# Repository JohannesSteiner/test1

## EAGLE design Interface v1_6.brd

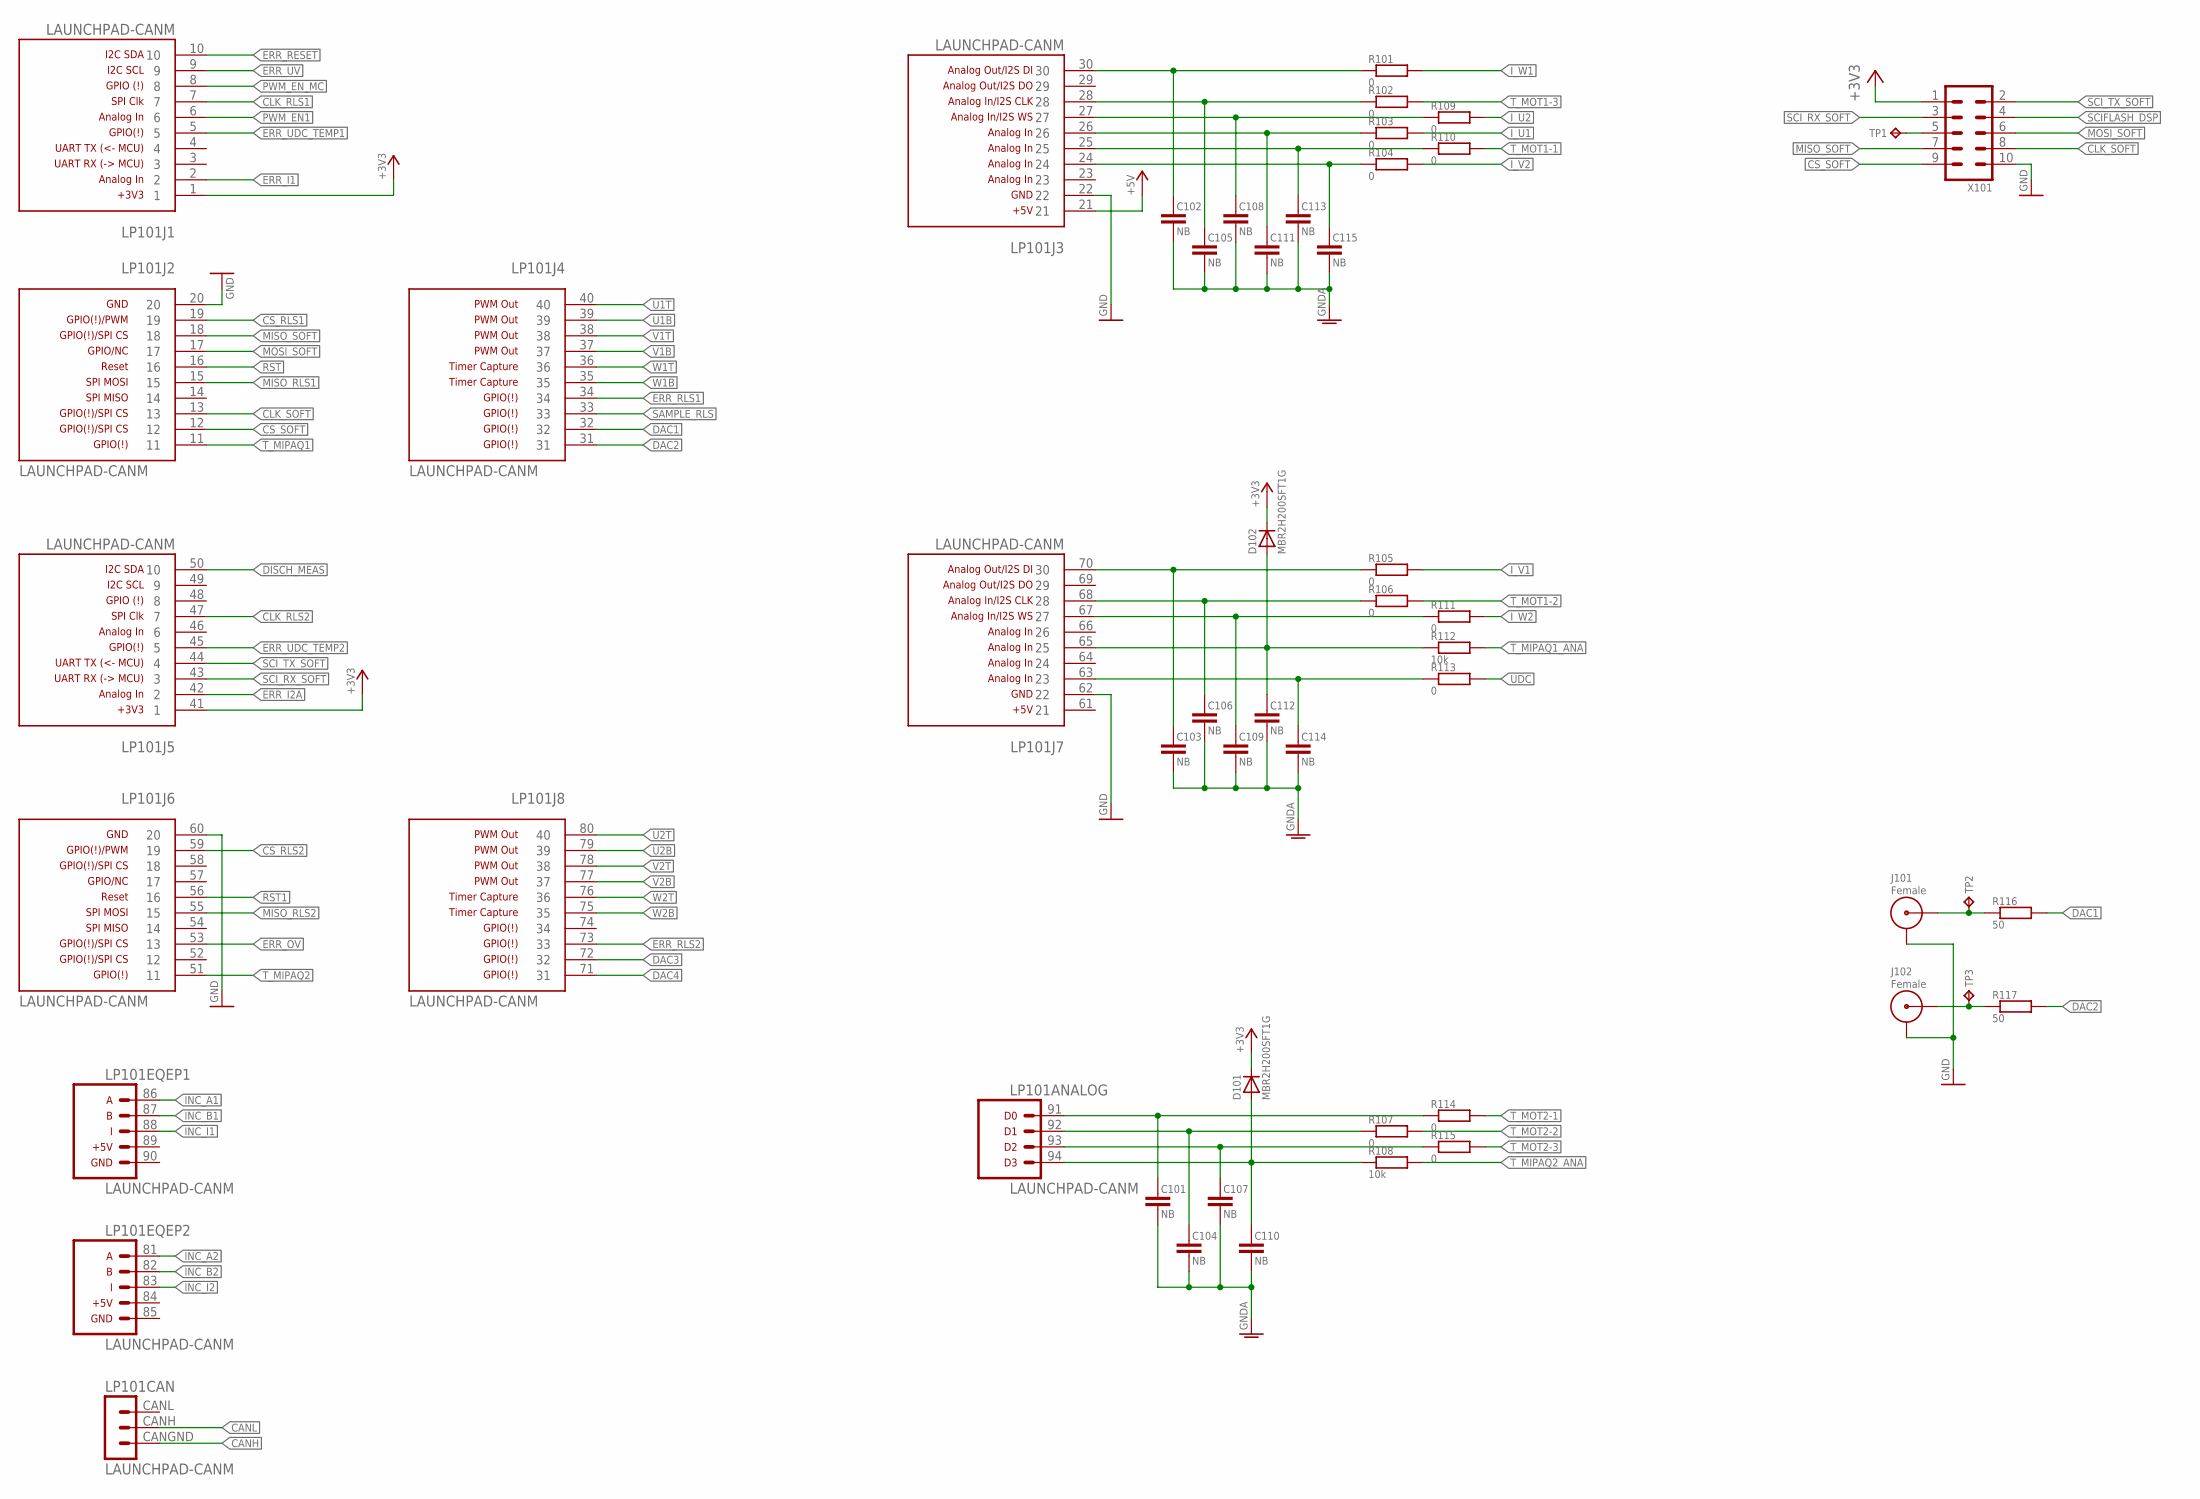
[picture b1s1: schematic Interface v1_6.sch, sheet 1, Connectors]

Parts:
C101, C102, C103, C104, C105, C106, C107, C108, C109, C110, C111, C112, C113, C114, C115: NB; C-0805"
D101, D102: MBR2H200SFT1G; D-0805"
J101, J102: Female; SMA_KLEIN
LP101: LAUNCHPAD-CANM; LAUNCHPAD_M
R101, R102, R103, R104, R105, R106, R107, R109, R110, R111, R113, R114, R115: 0; R-0805"
R108, R112: 10k; R-0805"
R116, R117: 50; R-0805"
TP1: TP-TH-08; TP-08
TP2, TP3: TP-TH-12; TP-12
X101: Softauge; ML-2~10

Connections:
+3V3: D101.C, D102.C, LP101.1, LP101.41 (1), X101.1; also elsewhere on the board
+5V: LP101.21; also elsewhere on the board
ADCIN15: C114.1, LP101.63 (23), R113.1
ADCINA0: C102.1, LP101.30, R101.1
ADCINA1: C103.1, LP101.70 (30), R105.1
ADCINA3: C111.1, LP101.26, R103.1
ADCINB2: C105.1, LP101.28, R102.1
ADCINB3: C113.1, LP101.25, R110.1
ADCINB4: C106.1, LP101.68 (28), R106.1
ADCINB5: C112.1, D102.A, LP101.65 (25), R112.1
ADCINC2: C108.1, LP101.27, R109.1
ADCINC3: C115.1, LP101.24, R104.1
ADCIND0: C101.1, LP101.91 (D0), R114.1
ADCIND1: C104.1, LP101.92 (D1), R107.1
ADCIND2: C107.1, LP101.93 (D2), R115.1
ADCIND3: C110.1, D101.A, LP101.94 (D3), R108.1
CANH: LP101.CANGND (1); also elsewhere on the board
CANL: LP101.CANH (2); also elsewhere on the board
CLK_RLS1: LP101.7; also elsewhere on the board
CLK_RLS2: LP101.47 (7); also elsewhere on the board
CLK_SOFT: LP101.13, X101.8
CS_RLS1: LP101.19; also elsewhere on the board
CS_RLS2: LP101.59 (19); also elsewhere on the board
CS_SOFT: LP101.12, X101.9
DAC1: LP101.32, R116.2
DAC2: LP101.31, R117.2
DAC3: LP101.72 (32)
DAC4: LP101.71 (31)
DISCH_MEAS: LP101.50 (10); also elsewhere on the board
ERR_I1: LP101.2; also elsewhere on the board
ERR_I2A: LP101.42 (2); also elsewhere on the board
ERR_OV: LP101.53 (13); also elsewhere on the board
ERR_RESET: LP101.10; also elsewhere on the board
ERR_RLS1: LP101.34
ERR_RLS2: LP101.73 (33)
ERR_UDC_TEMP1: LP101.5; also elsewhere on the board
ERR_UDC_TEMP2: LP101.45 (5); also elsewhere on the board
ERR_UV: LP101.9; also elsewhere on the board
GND: J101.1 (GND), J101.3 (GND), J101.4 (GND), J101.5 (GND), J102.1 (GND), J102.3 (GND), J102.4 (GND), J102.5 (GND), LP101.20, LP101.22, LP101.60 (20), LP101.62 (22), X101.10; also elsewhere on the board
GNDA: C101.2, C102.2, C103.2, C104.2, C105.2, C106.2, C107.2, C108.2, C109.2, C110.2, C111.2, C112.2, C113.2, C114.2, C115.2; also elsewhere on the board
INC_A1: LP101.86 (1); also elsewhere on the board
INC_A2: LP101.81 (1); also elsewhere on the board
INC_B1: LP101.87 (2); also elsewhere on the board
INC_B2: LP101.82 (2); also elsewhere on the board
INC_I1: LP101.88 (3); also elsewhere on the board
INC_I2: LP101.83 (3); also elsewhere on the board
I_U1: R103.2; also elsewhere on the board
I_U2: R109.2; also elsewhere on the board
I_V1: R105.2; also elsewhere on the board
I_V2: R104.2; also elsewhere on the board
I_W1: R101.2; also elsewhere on the board
I_W2: R111.2; also elsewhere on the board
MISO_RLS1: LP101.15; also elsewhere on the board
MISO_RLS2: LP101.55 (15); also elsewhere on the board
MISO_SOFT: LP101.18, X101.7
MOSI_SOFT: LP101.17, X101.6
unnamed: C109.1, LP101.67 (27), R111.1
unnamed: TP1.TP, X101.5
unnamed: J102.SIG, R117.1, TP3.TP
unnamed: J101.SIG, R116.1, TP2.TP
PWM_EN1: LP101.6; also elsewhere on the board
PWM_EN_MC: LP101.8; also elsewhere on the board
RST: LP101.16
RST1: LP101.56 (16)
SAMPLE_RLS: LP101.33; also elsewhere on the board
SCIFLASH_DSP: X101.4
SCI_RX_SOFT: LP101.43 (3), X101.3
SCI_TX_SOFT: LP101.44 (4), X101.2
T_MIPAQ1: LP101.11; also elsewhere on the board
T_MIPAQ1_ANA: R112.2; also elsewhere on the board
T_MIPAQ2: LP101.51 (11); also elsewhere on the board
T_MIPAQ2_ANA: R108.2; also elsewhere on the board
T_MOT1-1: R110.2; also elsewhere on the board
T_MOT1-2: R106.2; also elsewhere on the board
T_MOT1-3: R102.2; also elsewhere on the board
T_MOT2-1: R114.2; also elsewhere on the board
T_MOT2-2: R107.2; also elsewhere on the board
T_MOT2-3: R115.2; also elsewhere on the board
U1B: LP101.39; also elsewhere on the board
U1T: LP101.40; also elsewhere on the board
U2B: LP101.79 (39); also elsewhere on the board
U2T: LP101.80 (40); also elsewhere on the board
UDC: R113.2; also elsewhere on the board
V1B: LP101.37; also elsewhere on the board
V1T: LP101.38; also elsewhere on the board
V2B: LP101.77 (37); also elsewhere on the board
V2T: LP101.78 (38); also elsewhere on the board
W1B: LP101.35; also elsewhere on the board
W1T: LP101.36; also elsewhere on the board
W2B: LP101.75 (35); also elsewhere on the board
W2T: LP101.76 (36); also elsewhere on the board

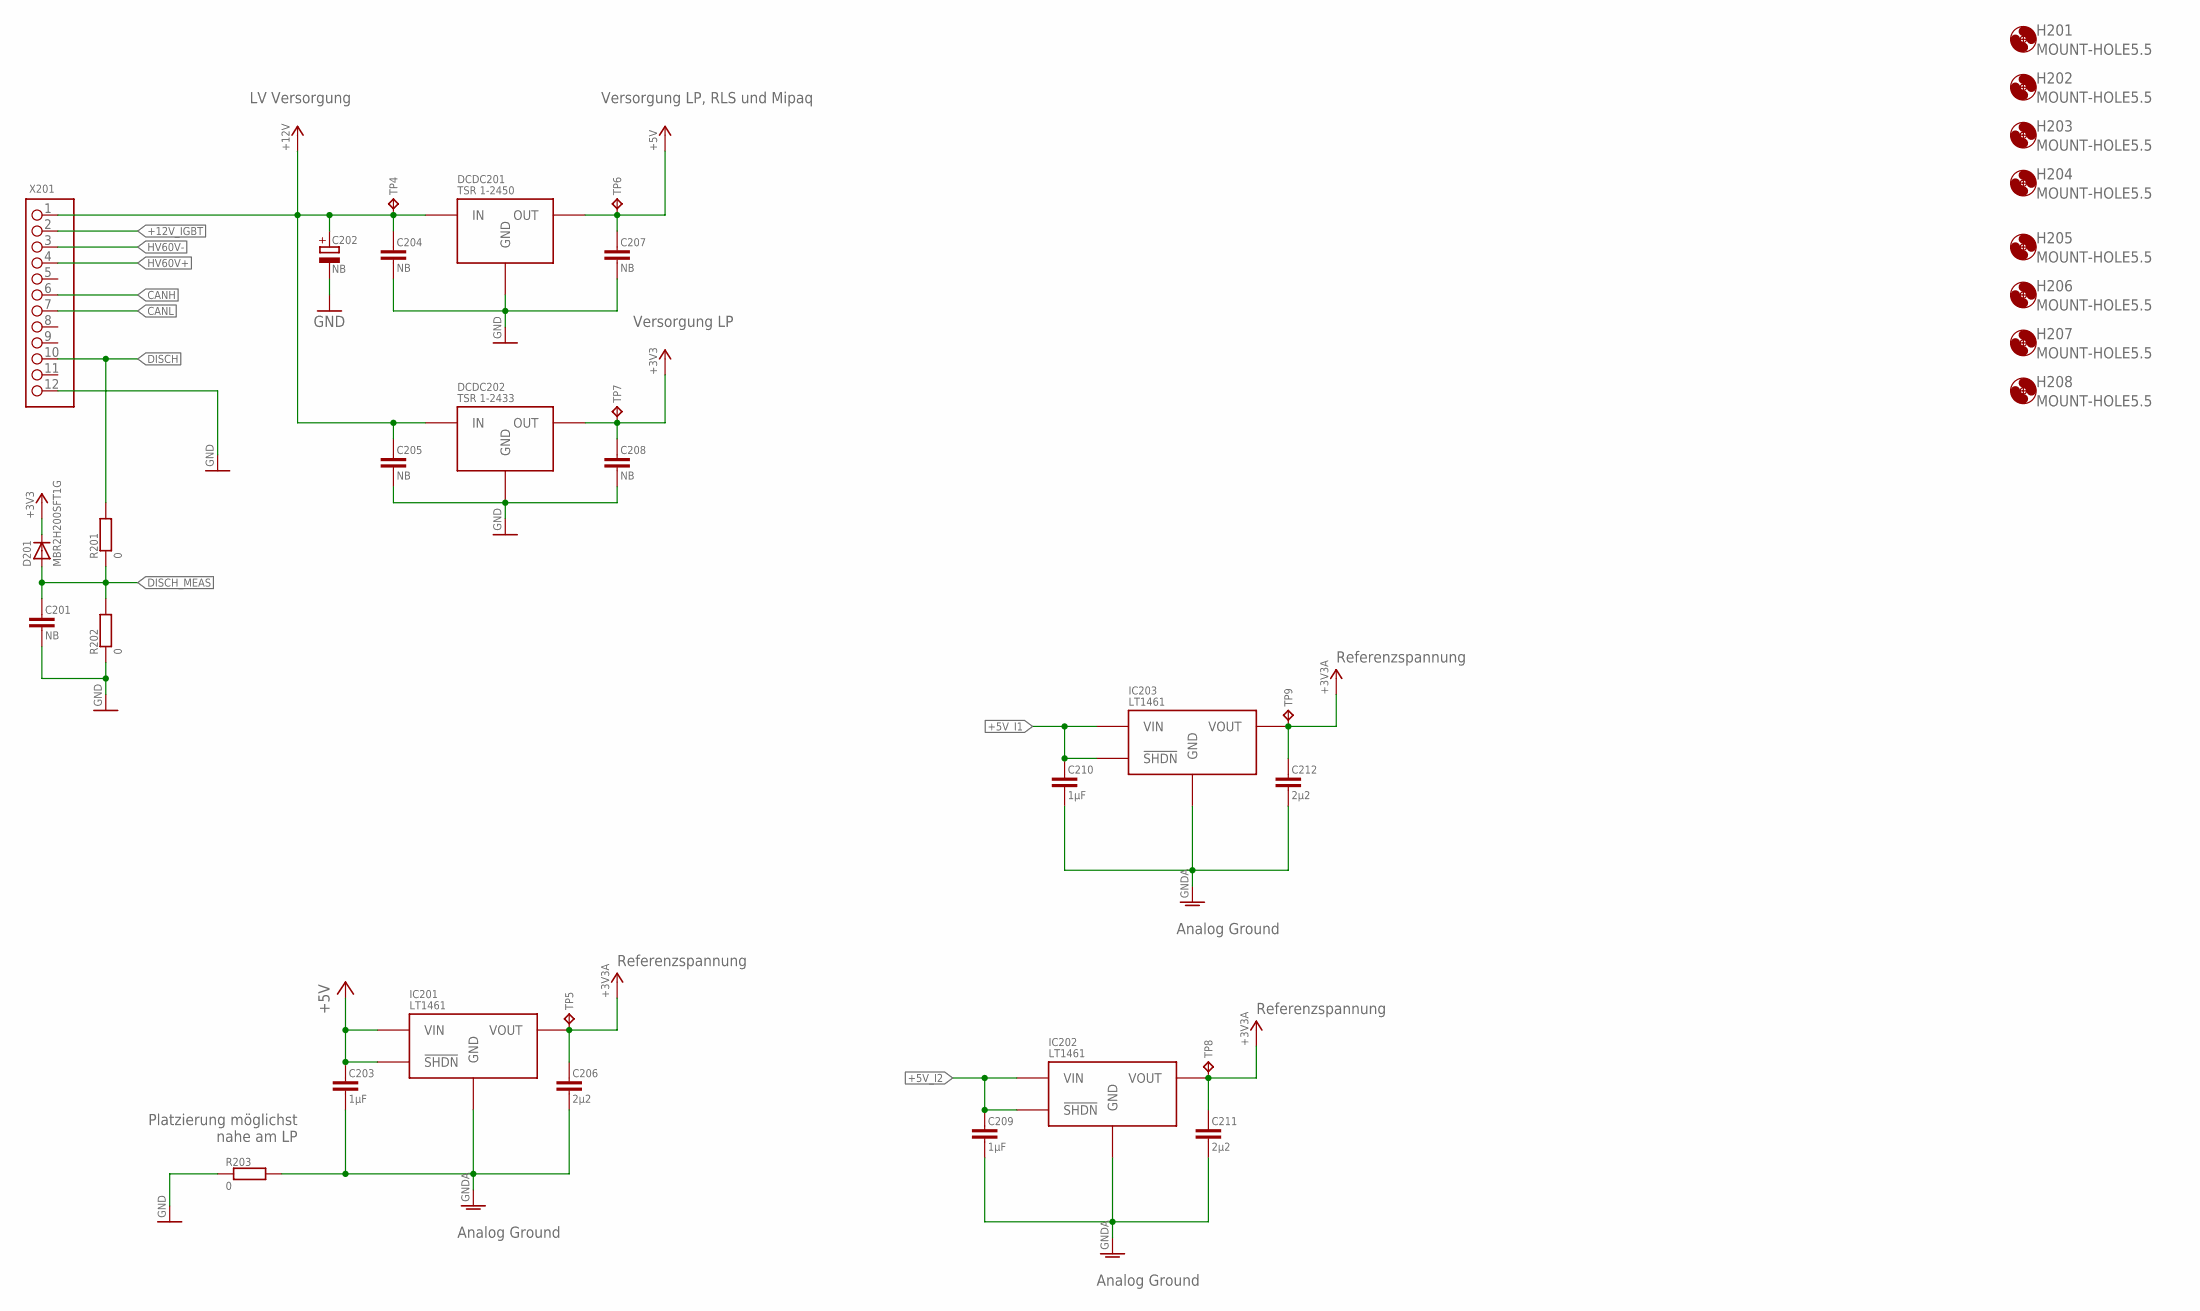
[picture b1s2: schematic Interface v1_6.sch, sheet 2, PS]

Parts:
C201, C204, C205, C207, C208: NB; C-0805"
C202: NB; CP-1210"
C203, C209, C210: 1µF; C-0805"
C206, C211, C212: 2µ2; C-0805"
D201: MBR2H200SFT1G; D-0805"
DCDC201: TSR 1-2450; TSR-1
DCDC202: TSR 1-2433; TSR-1
H201, H202, H203, H204, H205, H206, H207, H208: MOUNT-HOLE5.5; 5,5
IC201, IC202, IC203: LT1461; SO8
R201, R202, R203: 0; R-0805"
TP4, TP5, TP6, TP7, TP8, TP9: TP-TH-12; TP-12
X201: MINIBRIDGE12-GERADE

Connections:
+3V3: C208.1, D201.C, DCDC202.3 (OUT), TP7.TP; also elsewhere on the board
+3V3A: C206.1, IC201.6 (VOUT), TP5.TP; also elsewhere on the board
+3V3A_I1: C212.1, IC203.6 (VOUT), TP9.TP; also elsewhere on the board
+3V3A_I2: C211.1, IC202.6 (VOUT), TP8.TP; also elsewhere on the board
+5V: C203.1, C207.1, DCDC201.3 (OUT), IC201.2 (VIN), IC201.3 (!SHDN), TP6.TP; also elsewhere on the board
+5V_I1: C210.1, IC203.2 (VIN), IC203.3 (!SHDN); also elsewhere on the board
+5V_I2: C209.1, IC202.2 (VIN), IC202.3 (!SHDN); also elsewhere on the board
+12V: C202.+, C204.1, C205.1, DCDC201.1 (IN), DCDC202.1 (IN), TP4.TP, X201.1; also elsewhere on the board
+12V_IGBT: X201.2; also elsewhere on the board
CANH: X201.6; also elsewhere on the board
CANL: X201.7; also elsewhere on the board
DISCH: R201.2, X201.10; also elsewhere on the board
DISCH_MEAS: C201.1, D201.A, R201.1, R202.2; also elsewhere on the board
GND: C201.2, C202.-, C204.2, C205.2, C207.2, C208.2, DCDC201.2 (GND), DCDC202.2 (GND), R202.1, R203.1, X201.12; also elsewhere on the board
GNDA: C203.2, C206.2, C209.2, C210.2, C211.2, C212.2, IC201.4 (GND), IC202.4 (GND), IC203.4 (GND), R203.2; also elsewhere on the board
HV60V+: X201.4; also elsewhere on the board
HV60V-: X201.3; also elsewhere on the board

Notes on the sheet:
LV Versorgung
Versorgung LP, RLS und Mipaq
Versorgung LP
Referenzspannung
Analog Ground
Platzierung möglichst nahe am LP

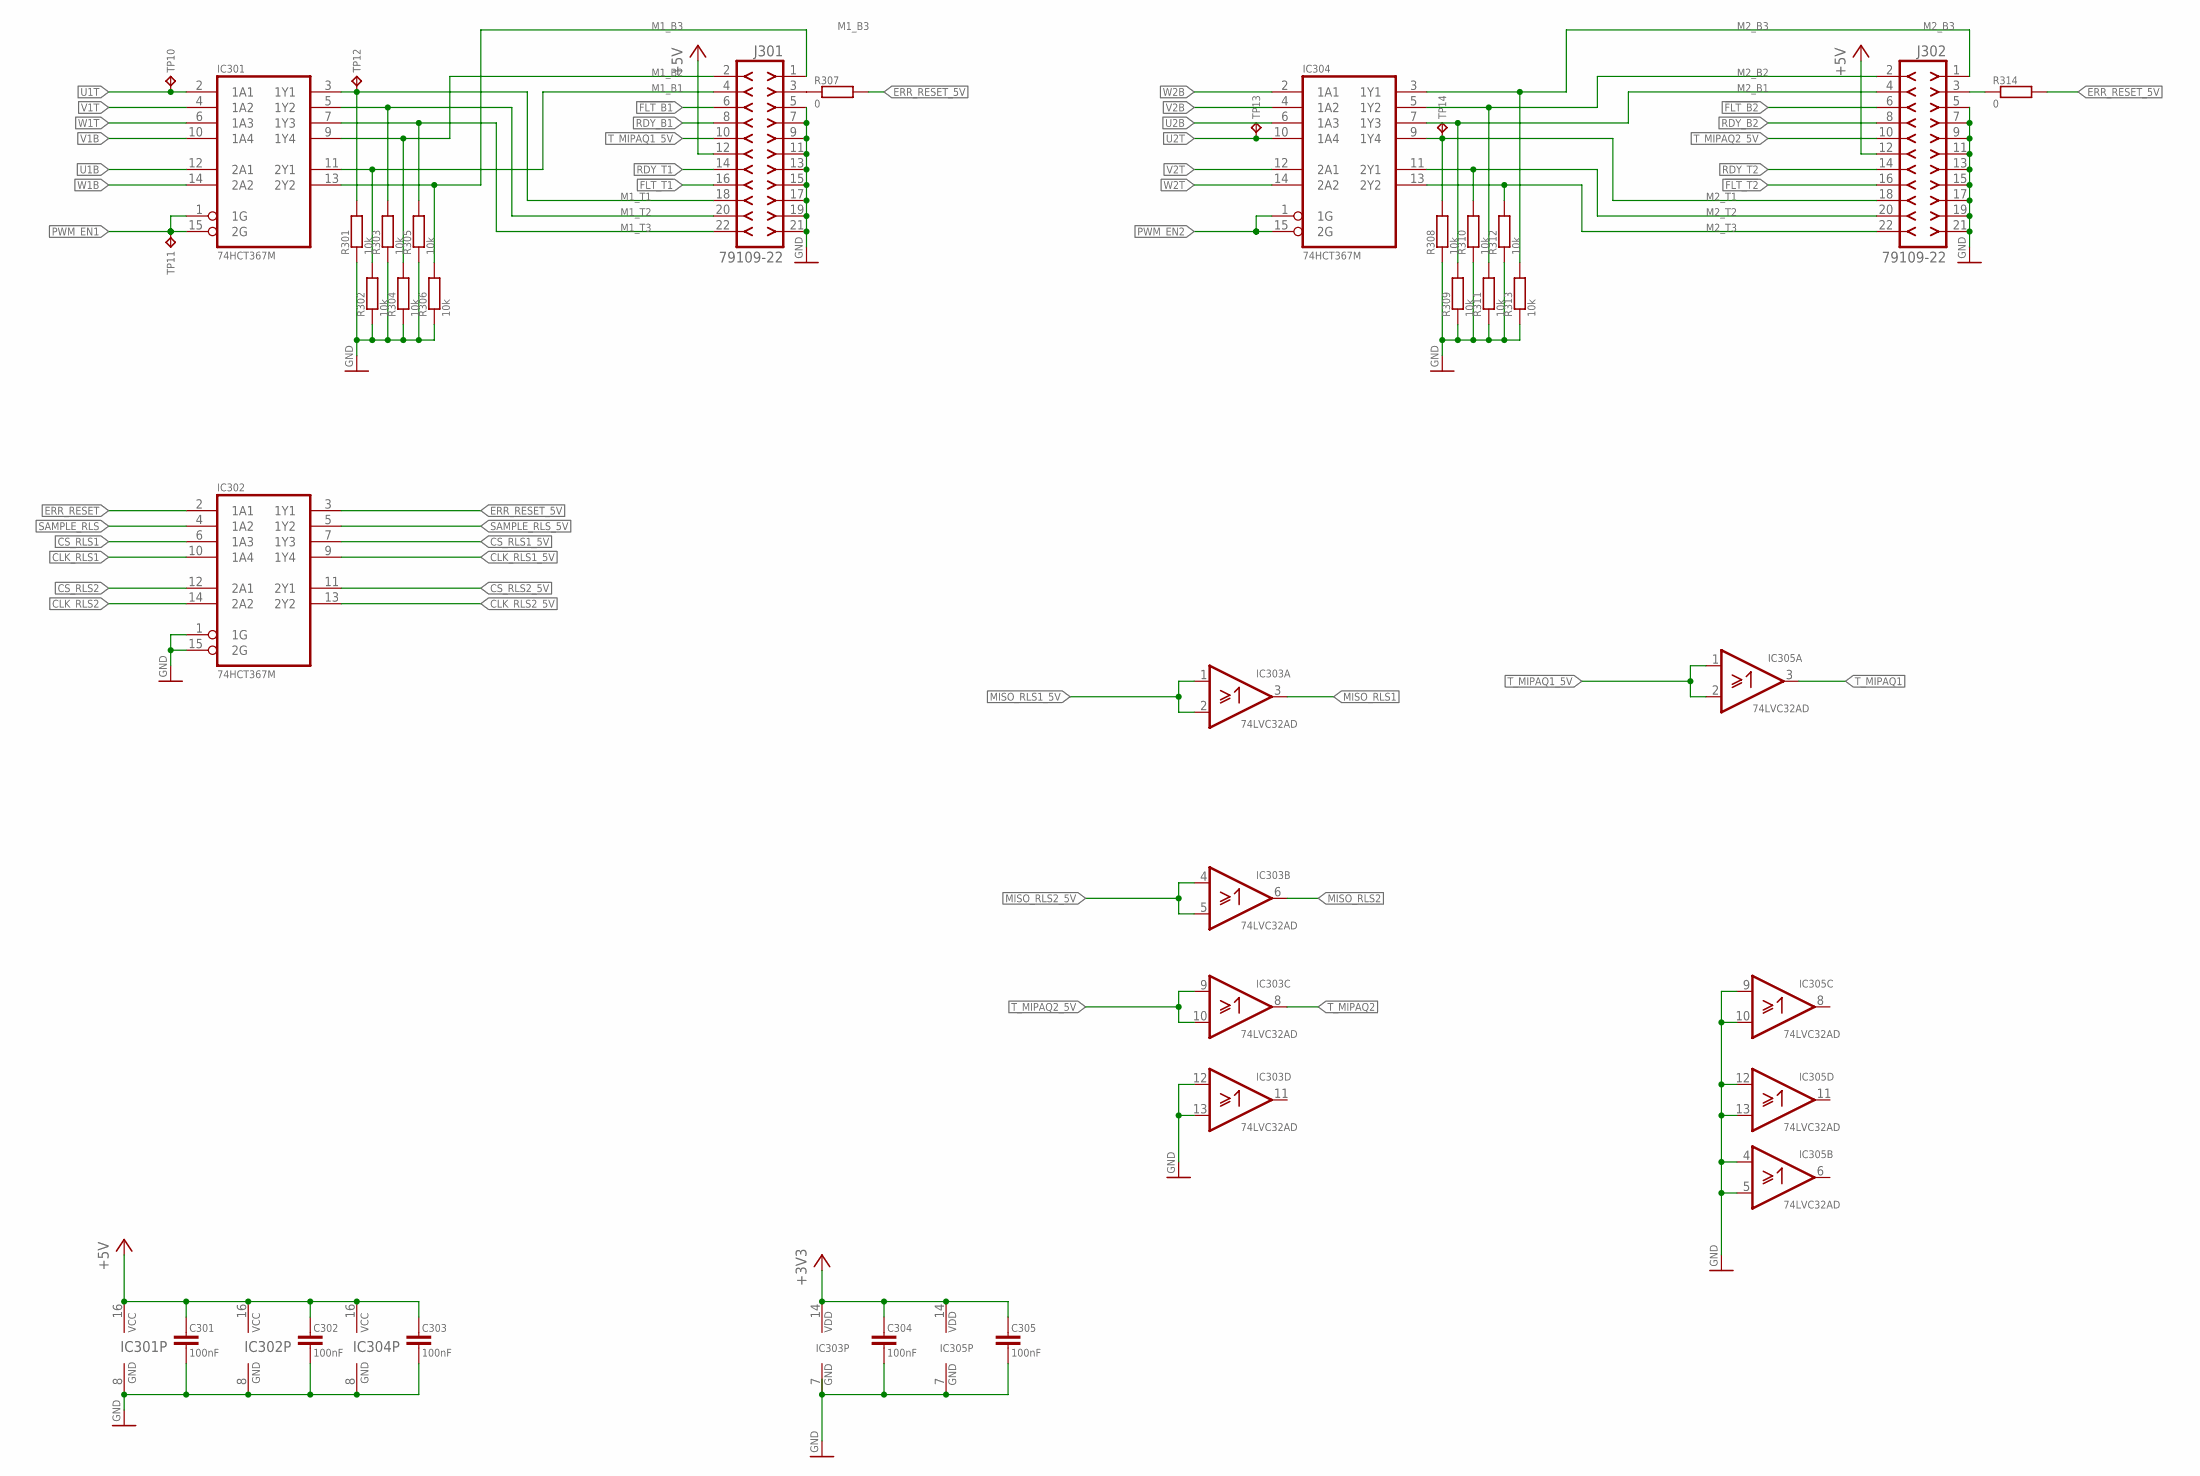
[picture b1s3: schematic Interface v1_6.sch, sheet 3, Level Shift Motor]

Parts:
C301, C302, C303, C304, C305: 100nF; C-0805"
IC301, IC302, IC304: 74HCT367M; SOIC16
IC303, IC305: 74LVC32AD; SOIC14
J301, J302: 79109-22
R301, R302, R303, R304, R305, R306, R308, R309, R310, R311, R312, R313: 10k; R-0805"
R307, R314: 0; R-0805"
TP10, TP11, TP12, TP13, TP14: TP-TH-08; TP-08

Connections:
!FLT_B1: J301.6; also elsewhere on the board
!FLT_B2: J302.6; also elsewhere on the board
!FLT_T1: J301.16; also elsewhere on the board
!FLT_T2: J302.16; also elsewhere on the board
+3V3: C304.1, C305.1, IC303.14 (VDD), IC305.14 (VDD); also elsewhere on the board
+5V: C301.1, C302.1, C303.1, IC301.16 (VCC), IC302.16 (VCC), IC304.16 (VCC), J301.12, J302.12; also elsewhere on the board
CLK_RLS1: IC302.10 (1A4); also elsewhere on the board
CLK_RLS1_5V: IC302.9 (1Y4); also elsewhere on the board
CLK_RLS2: IC302.14 (2A2); also elsewhere on the board
CLK_RLS2_5V: IC302.13 (2Y2); also elsewhere on the board
CS_RLS1: IC302.6 (1A3); also elsewhere on the board
CS_RLS1_5V: IC302.7 (1Y3); also elsewhere on the board
CS_RLS2: IC302.12 (2A1); also elsewhere on the board
CS_RLS2_5V: IC302.11 (2Y1); also elsewhere on the board
ERR_RESET: IC302.2 (1A1); also elsewhere on the board
ERR_RESET_5V: IC302.3 (1Y1), R307.2, R314.2; also elsewhere on the board
GND: C301.2, C302.2, C303.2, C304.2, C305.2, IC301.8 (GND), IC302.1 (1G), IC302.8 (GND), IC302.15 (2G), IC303.7 (GND), IC303.12 (A), IC303.13 (B), IC304.8 (GND), IC305.4 (A), IC305.5 (B), IC305.7 (GND), IC305.9 (A), IC305.10 (B), IC305.12 (A), IC305.13 (B), J301.5, J301.7, J301.9, J301.11, J301.13, J301.15, J301.17, J301.19, J301.21, J302.5, J302.7, J302.9, J302.11, J302.13, J302.15, J302.17, J302.19, J302.21, R301.1, R302.1, R303.1, R304.1, R305.1, R306.1, R308.1, R309.1, R310.1, R311.1, R312.1, R313.1; also elsewhere on the board
M1_B1: IC301.11 (2Y1), J301.4, R302.2
M1_B2: IC301.9 (1Y4), J301.2, R304.2
M1_B3: IC301.13 (2Y2), J301.1, R306.2
M1_T1: IC301.3 (1Y1), J301.18, R301.2, TP12.TP
M1_T2: IC301.5 (1Y2), J301.20, R303.2
M1_T3: IC301.7 (1Y3), J301.22, R305.2
M2_B1: IC304.7 (1Y3), J302.4, R309.2
M2_B2: IC304.5 (1Y2), J302.2, R311.2
M2_B3: IC304.3 (1Y1), J302.1, R313.2
M2_T1: IC304.9 (1Y4), J302.18, R308.2, TP14.TP
M2_T2: IC304.11 (2Y1), J302.20, R310.2
M2_T3: IC304.13 (2Y2), J302.22, R312.2
MISO_RLS1: IC303.3 (Y); also elsewhere on the board
MISO_RLS1_5V: IC303.1 (A), IC303.2 (B); also elsewhere on the board
MISO_RLS2: IC303.6 (Y); also elsewhere on the board
MISO_RLS2_5V: IC303.4 (A), IC303.5 (B); also elsewhere on the board
unnamed: J301.3, R307.1
unnamed: J302.3, R314.1
PWM_EN1: IC301.1 (1G), IC301.15 (2G), TP11.TP; also elsewhere on the board
PWM_EN2: IC304.1 (1G), IC304.15 (2G); also elsewhere on the board
RDY_B1: J301.8; also elsewhere on the board
RDY_B2: J302.8; also elsewhere on the board
RDY_T1: J301.14; also elsewhere on the board
RDY_T2: J302.14; also elsewhere on the board
SAMPLE_RLS: IC302.4 (1A2); also elsewhere on the board
SAMPLE_RLS_5V: IC302.5 (1Y2); also elsewhere on the board
T_MIPAQ1: IC305.3 (Y); also elsewhere on the board
T_MIPAQ1_5V: IC305.1 (A), IC305.2 (B), J301.10; also elsewhere on the board
T_MIPAQ2: IC303.8 (Y); also elsewhere on the board
T_MIPAQ2_5V: IC303.9 (A), IC303.10 (B), J302.10; also elsewhere on the board
U1B: IC301.12 (2A1); also elsewhere on the board
U1T: IC301.2 (1A1), TP10.TP; also elsewhere on the board
U2B: IC304.6 (1A3); also elsewhere on the board
U2T: IC304.10 (1A4), TP13.TP; also elsewhere on the board
V1B: IC301.10 (1A4); also elsewhere on the board
V1T: IC301.4 (1A2); also elsewhere on the board
V2B: IC304.4 (1A2); also elsewhere on the board
V2T: IC304.12 (2A1); also elsewhere on the board
W1B: IC301.14 (2A2); also elsewhere on the board
W1T: IC301.6 (1A3); also elsewhere on the board
W2B: IC304.2 (1A1); also elsewhere on the board
W2T: IC304.14 (2A2); also elsewhere on the board

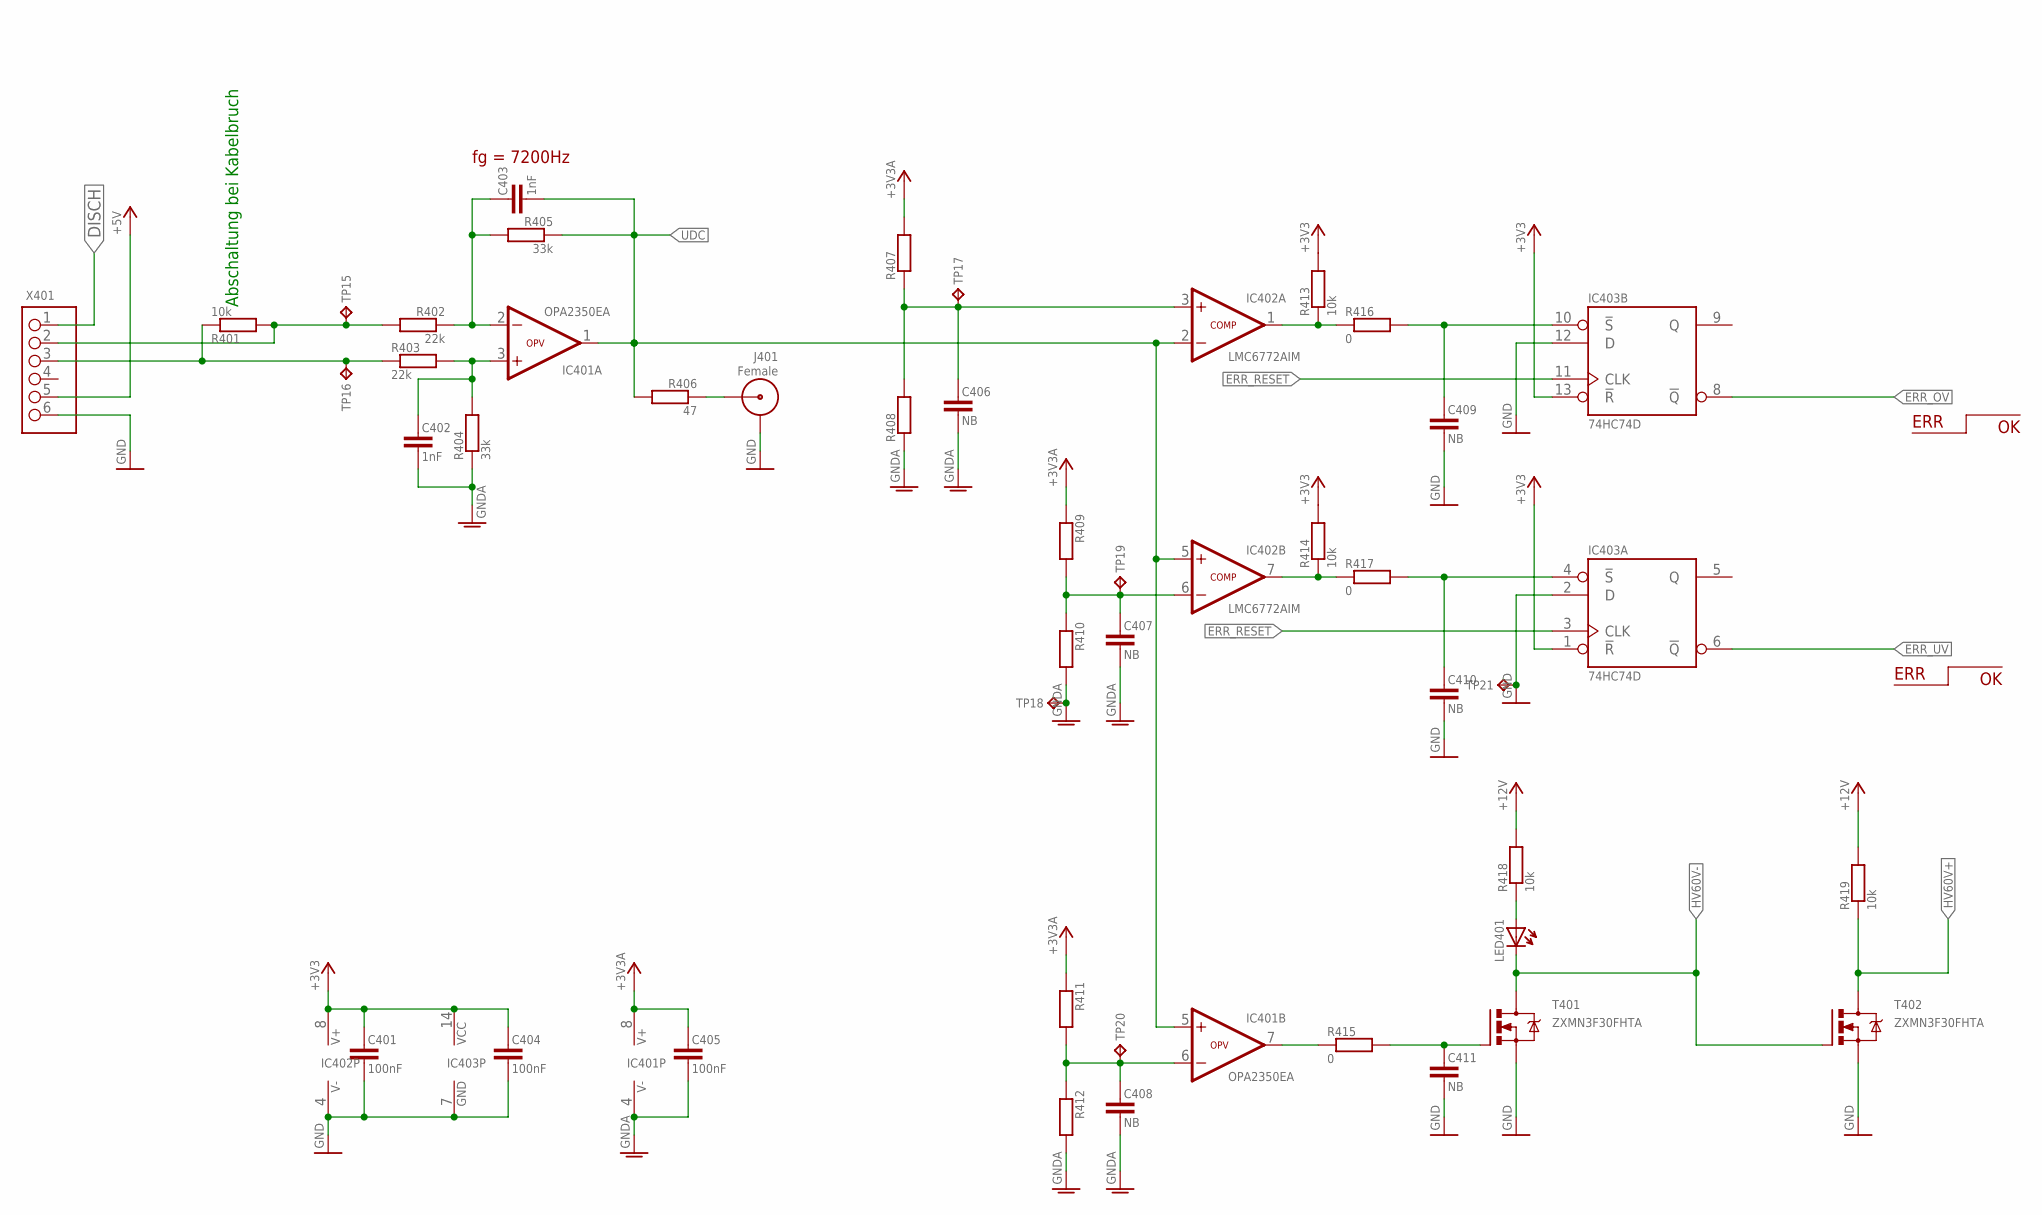
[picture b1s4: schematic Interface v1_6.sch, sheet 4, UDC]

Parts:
C401, C404, C405: 100nF; C-0805"
C402, C403: 1nF; C-0805"
C406, C407, C408, C409, C410, C411: NB; C-0805"
IC401: OPA2350EA; SOIC8
IC402: LMC6772AIM; SOIC8
IC403: 74HC74D; SOIC14
J401: Female; SMA_KLEIN
LED401: LED-0805"
R401, R413, R414, R418, R419: 10k; R-0805"
R402, R403: 22k; R-0805"
R404, R405: 33k; R-0805"
R406: 47; R-0805"
R407, R408, R409, R410, R411, R412: R-0805"
R415, R416, R417: 0; R-0805"
T401, T402: ZXMN3F30FHTA; SOT23
TP15, TP16, TP17, TP19, TP20, TP21: TP-TH-08; TP-08
TP18: TP-TH-12; TP-12
X401: UDC_Messung; MINIBRIDGE6-ABGEWINKELT

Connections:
+3V3: C401.1, C404.1, IC402.8 (V+), IC403.1 (!R), IC403.13 (!R), IC403.14 (VCC), R413.2, R414.2; also elsewhere on the board
+3V3A: C405.1, IC401.8 (V+), R407.2, R409.1, R411.1; also elsewhere on the board
+5V: X401.5; also elsewhere on the board
+12V: R418.2, R419.2; also elsewhere on the board
DISCH: X401.1; also elsewhere on the board
ERR_OV: IC403.8 (!Q); also elsewhere on the board
ERR_RESET: IC403.3 (CLK), IC403.11 (CLK); also elsewhere on the board
ERR_UV: IC403.6 (!Q); also elsewhere on the board
GND: C401.2, C404.2, C409.2, C410.2, C411.2, IC402.4 (V-), IC403.2 (D), IC403.7 (GND), IC403.12 (D), J401.1 (GND), J401.3 (GND), J401.4 (GND), J401.5 (GND), T401.2 (S), T402.2 (S), TP21.TP, X401.6; also elsewhere on the board
GNDA: C402.2, C405.2, C406.2, C407.2, C408.2, IC401.4 (V-), R404.1, R408.1, R410.2, R412.2, TP18.TP; also elsewhere on the board
HV60V+: R419.1, T402.3 (D); also elsewhere on the board
HV60V-: LED401.C, T401.3 (D), T402.1 (G); also elsewhere on the board
unnamed: LED401.A, R418.1
unnamed: J401.SIG, R406.1
unnamed: C403.1, IC401.2 (-IN), R402.1, R405.2
unnamed: C402.1, IC401.3 (+IN), R403.2, R404.2
unnamed: IC402.7 (OUT), R414.1, R417.1
unnamed: IC402.1 (OUT), R413.1, R416.1
unnamed: C410.1, IC403.4 (!S), R417.2
unnamed: C409.1, IC403.10 (!S), R416.2
unnamed: C406.1, IC402.3 (+IN), R407.1, R408.2, TP17.TP
unnamed: C407.1, IC402.6 (-IN), R409.2, R410.1, TP19.TP
unnamed: C408.1, IC401.6 (-IN), R411.2, R412.1, TP20.TP
unnamed: IC401.7 (OUT), R415.1
unnamed: C411.1, R415.2, T401.1 (G)
UDC: C403.2, IC401.1 (OUT), IC401.5 (+IN), IC402.2 (-IN), IC402.5 (+IN), R405.1, R406.2; also elsewhere on the board
VDC+: R401.1, R403.1, TP16.TP, X401.3
VDC-: R401.2, R402.2, TP15.TP, X401.2

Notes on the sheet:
ERR
fg = 7200Hz
Abschaltung bei Kabelbruch

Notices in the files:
parts and their libraries:
con-molex-milli-grid: Copyright (C) 2010, Bob Starr
